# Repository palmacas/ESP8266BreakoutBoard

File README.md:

# ESP8266 Breakout Board

Simple breakout board to make easy the ESP-01 programming and flash process. Ideal to use on a breadboard.

---
More information:  
[ESP8266 Breakout Board](http://palmacas.com/esp8266-breakout-board_en/) [[Spanish]](http://palmacas.com/esp8266-breakout-board/)

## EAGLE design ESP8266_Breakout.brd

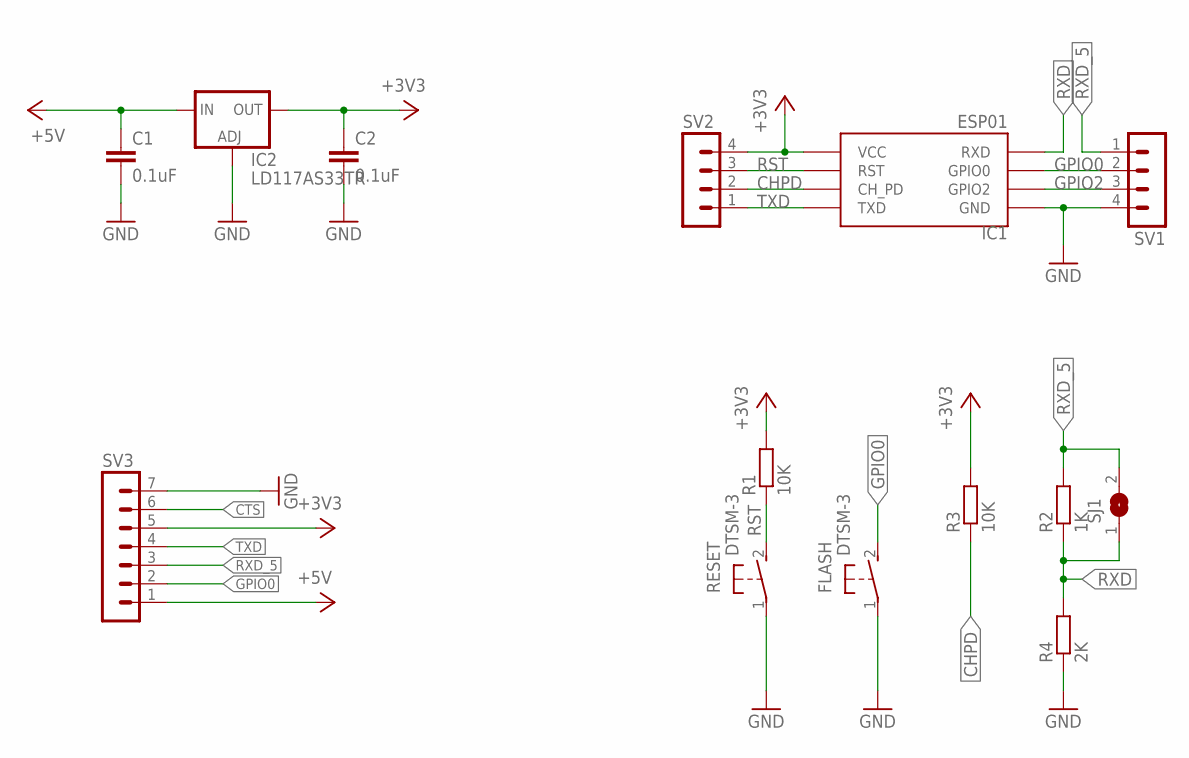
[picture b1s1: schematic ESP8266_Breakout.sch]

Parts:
C1, C2: 0.1uF; C0805K
FLASH: DTSM-3
IC1: ESP01
IC2: LD117AS33TR; SOT223
R1: 10K; M0805
R2: 1K; R0805
R3: 10K; R0805
R4: 2K; R0805
RESET: DTSM-3
SJ1: SJ
SV1, SV2: MA04-1
SV3: MA07-1

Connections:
+3V3: C2.1, IC1.VCC, IC2.4 (OUT), R1.2, R3.2, SV2.4, SV3.5
CHPD: IC1.CH_PD, R3.1, SV2.2
CTS: SV3.6
GND: C1.2, C2.2, FLASH.1, IC1.GND, IC2.1 (ADJ), R4.1, RESET.1, SV1.4, SV3.7
GPIO0: FLASH.2, IC1.GPIO0, SV1.2, SV3.2
GPIO2: IC1.GPIO2, SV1.3
RST: IC1.RST, R1.1, RESET.2, SV2.3
RXD: IC1.RX (RXD), R2.1, R4.2, SJ1.1
RXD_5: R2.2, SJ1.2, SV1.1, SV3.3
TXD: IC1.TX (TXD), SV2.1, SV3.4
V+: C1.1, IC2.3 (IN), SV3.1

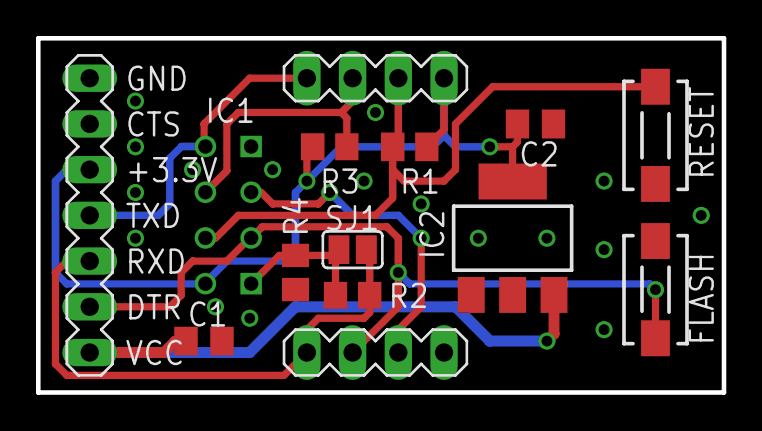
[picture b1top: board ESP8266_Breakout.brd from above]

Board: 2 copper layers, 38.1 x 19.7 mm, 14 parts (0 on the bottom side), 10 nets.

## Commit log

2020-06-03 Update LICENSE
